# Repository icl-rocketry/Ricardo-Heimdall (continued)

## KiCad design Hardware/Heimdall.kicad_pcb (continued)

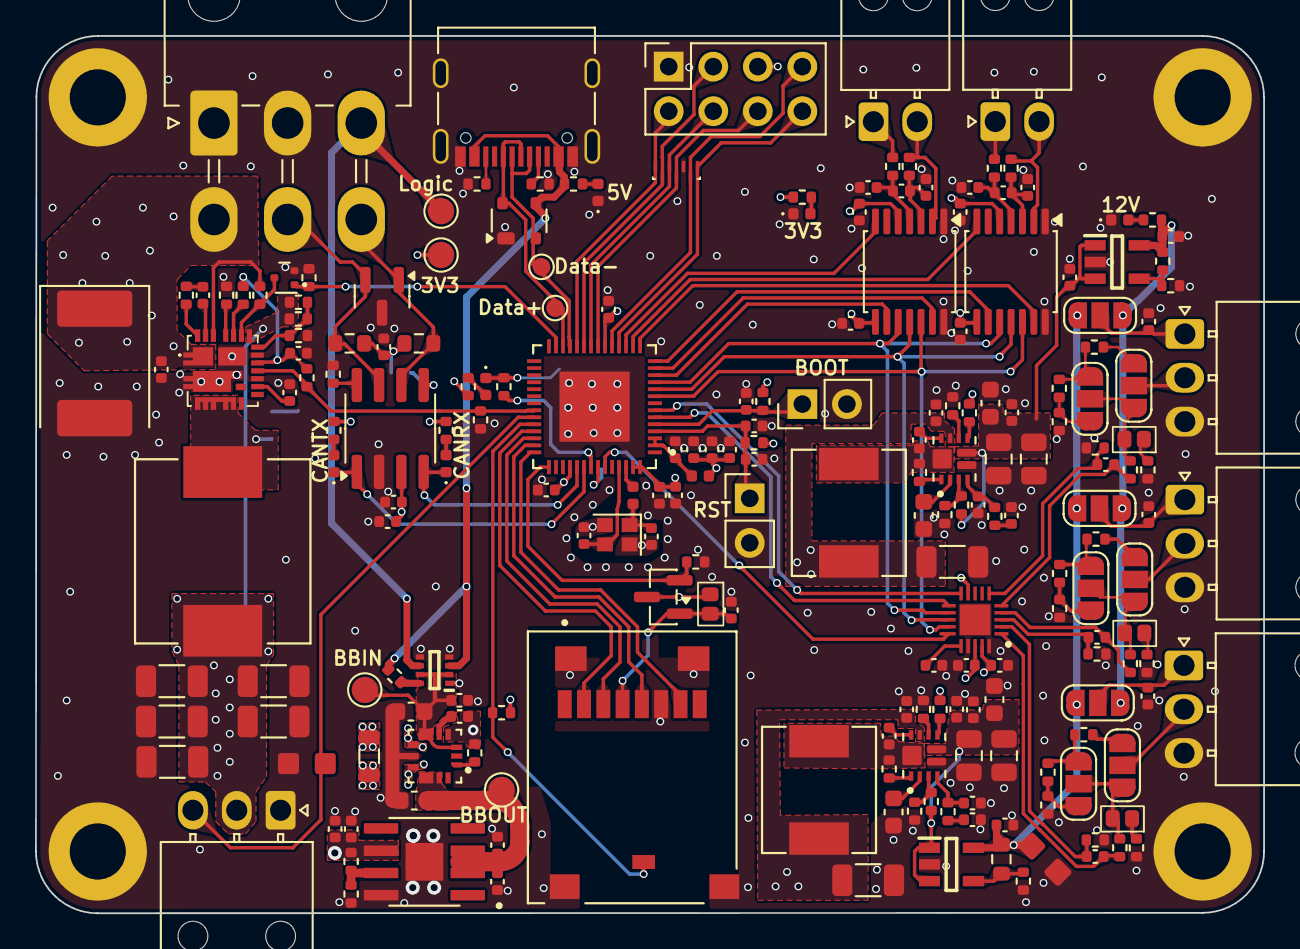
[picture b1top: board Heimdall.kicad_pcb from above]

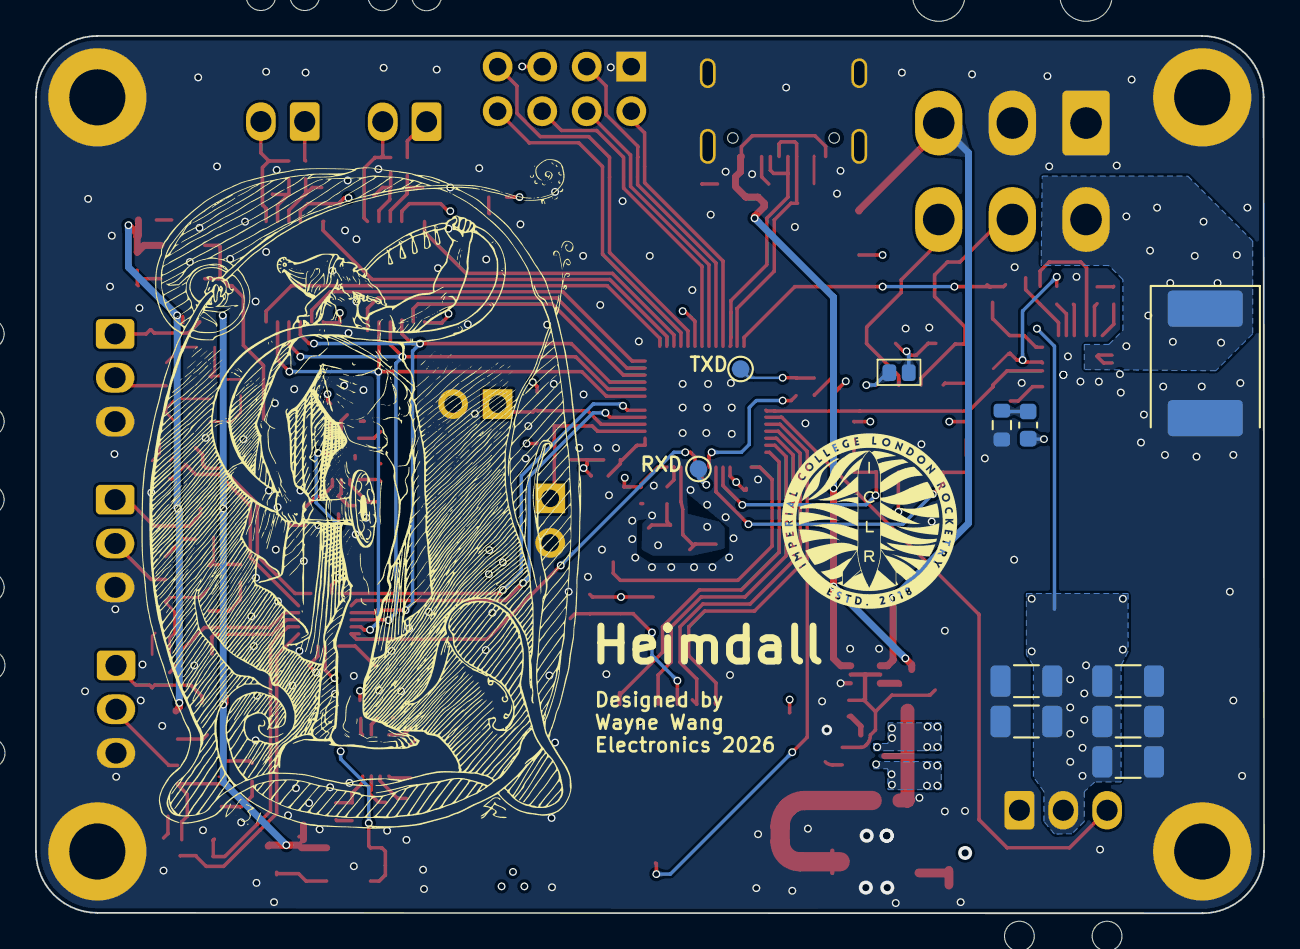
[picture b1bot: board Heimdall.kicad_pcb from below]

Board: 4 copper layers, 70.0 x 50.0 mm, 226 parts (12 on the bottom side), 139 nets.

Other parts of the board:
LOGO1: ICLR LOGO; iclr_logo_estd2018_10mm

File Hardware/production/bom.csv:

Designator,Footprint,Quantity,Value,LCSC Part #
"C101, C201, C205, C207, C502",0402,5,10uF,
"C102, C104, C107, C203, C301, C801, C802",0402,7,1uF,
"C103, C105, C106, C108, C110, C111, C208, C306, C310, C407, C409, C420, C421, C501, C701, C806, C807, C809, C902, C904, C905, C907, C909, C910",0402,24,100nF,
"C109, C804, C805, C808, C901, C903, C906, C908",0402,8,10nF,
"C112, C113",0402,2,11pF,
"C202, C414",0603,2,10uF,
C204,0603,1,22uF,
"C206, C302",0402,2,4.7uF,
"C303, C313",CP_EIA-7360-38_Kemet-E,2,100uF,T52M1107M035C0100
"C304, C305, C307, C308, C309, C312, C314, C315, C316, C317, C410",1206,11,47uF,
C311,0603,1,160pF,
C401,0603,1,2.2uF,
C402,0402,1,180pF,
C403,0402,1,3.9nF,
"C404, C413",0402,2,1uF,CL05X105KA5NQNC
"C405, C406, C417, C419",0805,4,22uF,
C408,0402,1,2.2uF, GRM155R61E225ME15D
C411,0603,1,10uF,TMK107BBJ106MA-T
"C412, C423",0402,2,100nF,C1005X5R1E104KT000E
C415,0402,1,120pF,
C416,0402,1,2.2nF,
C418,0402,1,2.2uF,GRM155R61E225ME15D
C422,0603,1,10uF, TMK107BBJ106MA-T
C424,1206,1,22uF,
C503,0402,1,47nF,
C803,0402,1,220nF,
D1001,RCLAMP3346PQTNT,1,RCLAMP3346PQTNT,
"D101, D102",0402,2,LED_GREEN,
D103,0402,1,LED_ORANGE,
D104,0402,1,LED_BLUE,
D105,0402,1,LED_RED,
D1101,CPD,1,CPDF3V3UP-HF,
D401,CPD,1,CPDF5V0U-HF,
D501,SOT-23,1,SM712_SOT23,
D601,SOT-143,1,SP0503BAHT,
D602,0402,1,LED_WHITE,
J103,Molex_Mini-Fit_Jr_5569-06A2_2x03_P4.20mm_Horizontal,1,RBUS,
"J1101, J801, J802, J803",Molex_Nano-Fit_105313-xx03_1x03_P2.50mm_Horizontal,4,1053131103,
J601,USB_C_Receptacle_Palconn_UTC16-G,1,USB_C_Receptacle_USB2.0,
J701,JAE_ST1W008S4TR2000,1,ST1W008S4TR2000,
"J901, J902",Molex_Nano-Fit_105313-xx02_1x02_P2.50mm_Horizontal,2,1053131102,
L101,0402,1,2nH,
L102,0402,1,20nH,
L201,0805,1,1uH,
L301,IND_SPM10065VT-3R3M-D,1,3.3uH,SPM10065VT-3R3M-D
"L401, L402",IND_SRP6540-390M,2,5uH,
LOGO1,iclr_logo_estd2018_10mm,1,ICLR LOGO,
Q301,SOT-723,1,"SSM3K15AMFV,L3F",
Q701,SOT-23,1,DMP3099L, DMP3099L
"R101, R105, R201, R204, R301, R303, R309, R404, R414, R702",0402,10,10kΩ,
"R102, R106",0402,2,470Ω,
"R103, R104, R305, R701, R807, R808, R811, R812, R816, R818",0402,10,1kΩ,
R107,0402,1,499Ω,
R108,0402,1,3kΩ,
R109,0402,1,18kΩ,
R202,0402,1,14kΩ,
R203,0402,1,56kΩ,
R302,0402,1,113kΩ,ERJ-2RKF1133X
R304,0402,1,2.2Ω,
R306,0402,1,442kΩ, ERJ-2RKF4423X 
R307,0402,1,200kΩ,
"R308, R403, R411",0402,3,100kΩ,
R310,0603,1,5.1Ω,
R401,0402,1,7.87kΩ,
R402,0402,1,360kΩ,
R405,0402,1,560kΩ,
"R406, R412",0402,2,49.9kΩ,
R407,0603,1,150kΩ,
R408,0402,1,301kΩ,
R409,0402,1,18.7kΩ,
R410,0402,1,976kΩ,
R413,0402,1,432kΩ,
R415,0402,1,475kΩ,
R416,0402,1,287kΩ,
R501,0402,1,0Ω,
"R502, R503",0603,2,60Ω,
"R601, R602, R603",0402,3,5.1kΩ,
"R801, R804, R813",0402,3,75kΩ,RT0402BRD0775KL
"R802, R805, R814",0402,3,14kΩ,0402WGF1402TCE
"R803, R806, R815",0402,3,10kΩ, ERA2ARB103X
"R809, R810, R817",0402,3,49.9Ω,RT0402BRD0749R9L
"R901, R902, R903, R904",0402,4,100Ω,
U101,QFN40P700X700X90-57N,1,ESP32-S3,
U201,SOTFL50P160X60-8N,1,LM66200DRLR,
U202,CONV_MAX77827AEFD+T,1,MAX77827AEFD+T,
U203,SOIC127P599X175-9N,1,SC4215ASTRT,
U301,SiC437BEDT1GE3,1,SiC437AED-T1,
U401,IC_TPS61089RNRR,1,TPS61089RNRR,
U402,SOT95P282X145-5N,1,AP2205-W5-7,
U403,SOT95P282X145-5N,1,AP2205-W5-7,AP2205-W5-7
U404,IC_TPS61089RNRR,1,TPS61089RNRR,TPS61089RNRR
U501,SOIC-8_3.9x4.9mm_P1.27mm,1,SN65HVD230,
U801,QFN40P300X300X80-21N-D,1,ADS131M04IRUKR,ADS131M04IRUKR
"U901, U902",TSSOP-14_4.4x5mm_P0.65mm,2,MAX31856,
Y101,Crystal_SMD_2016-4Pin_2.0x1.6mm,1,R940000171,

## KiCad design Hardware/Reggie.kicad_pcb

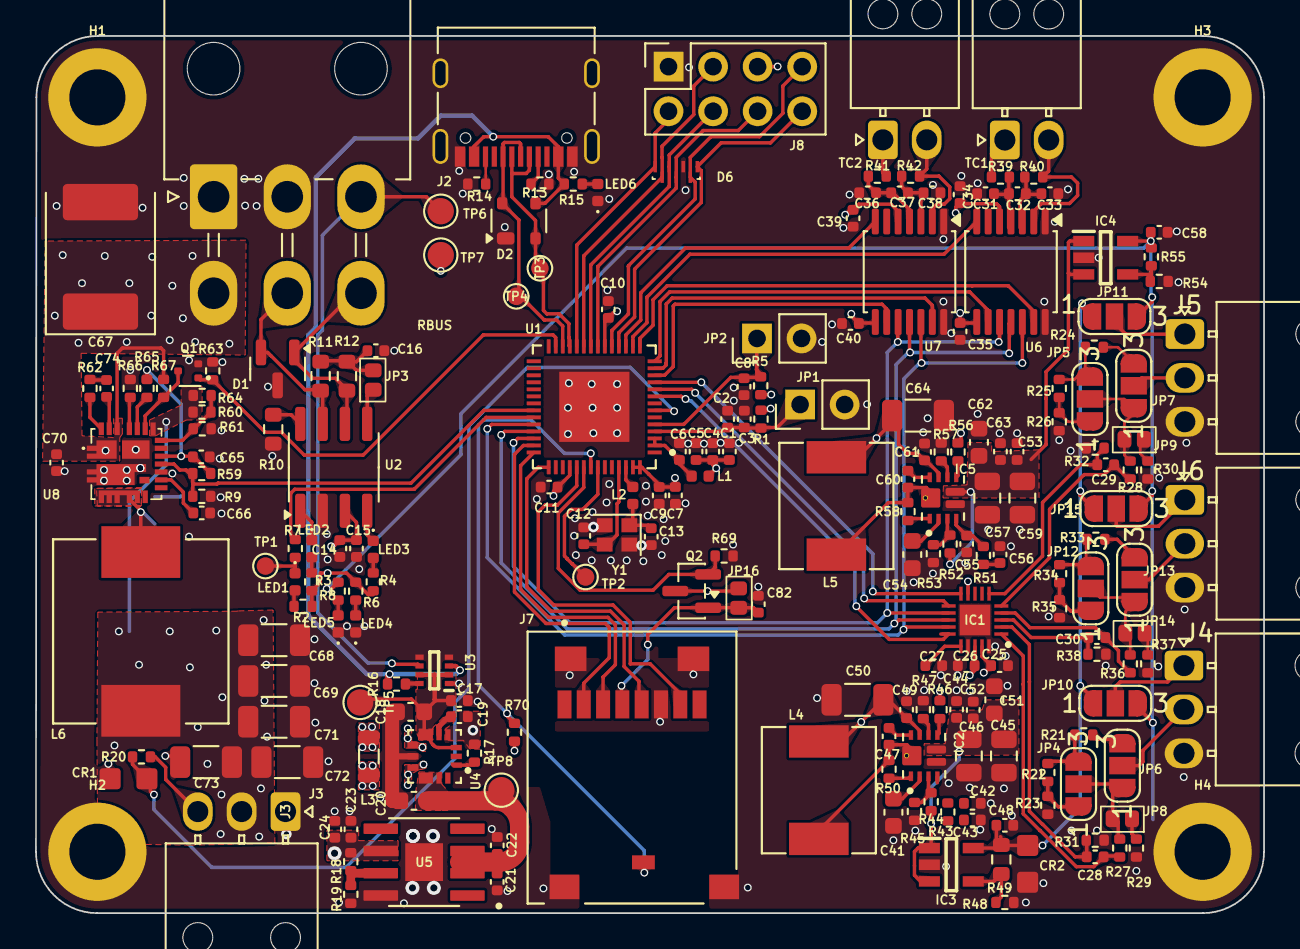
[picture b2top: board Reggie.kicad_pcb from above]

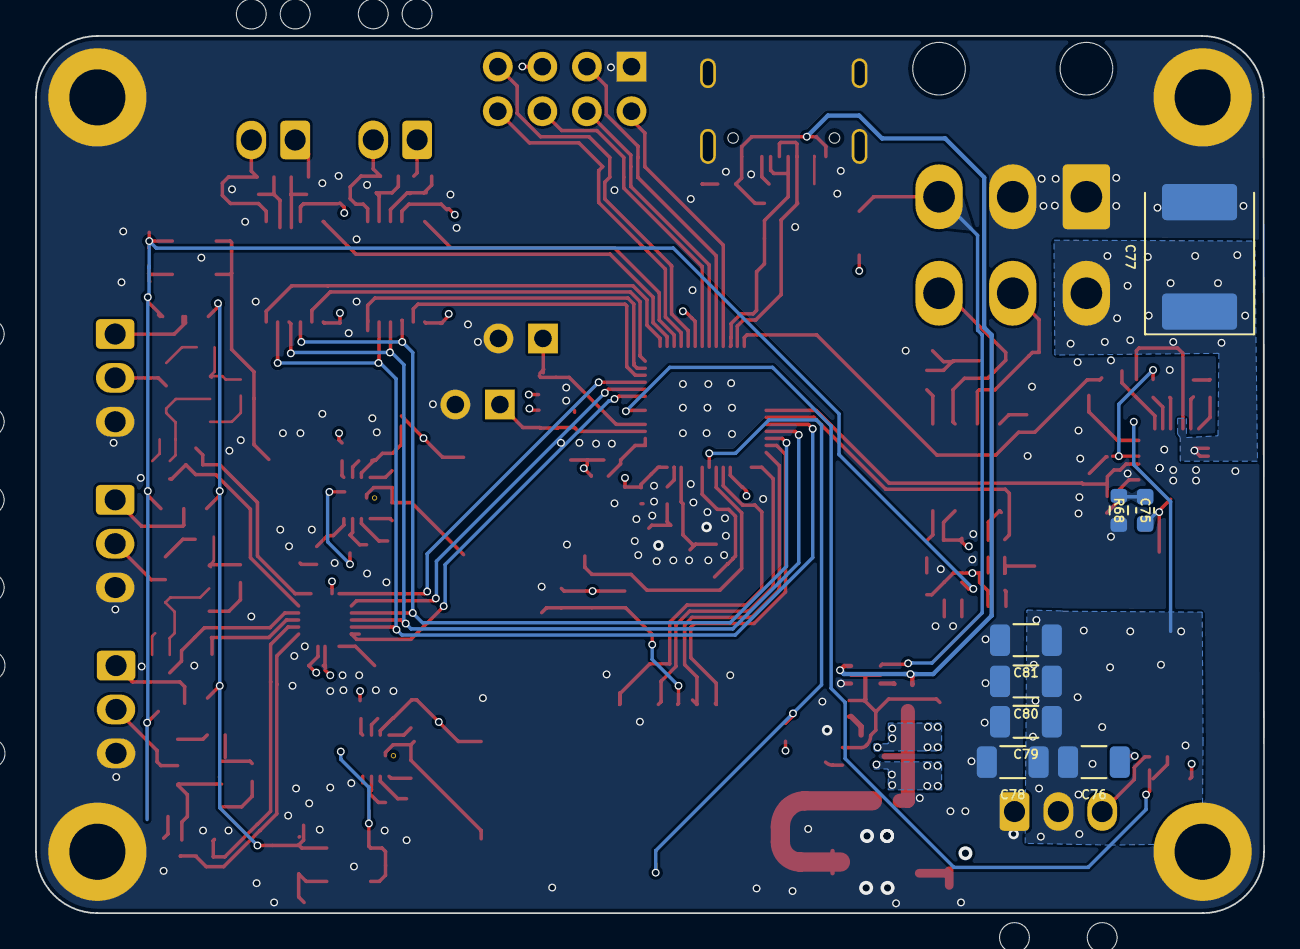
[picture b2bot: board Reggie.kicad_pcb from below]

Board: 4 copper layers, 70.0 x 50.0 mm, 223 parts (8 on the bottom side), 140 nets.

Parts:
C1, C15, C17, C21, C23: 10uF; C_0402_1005Metric
C2, C4, C7, C19, C25, C26, C44, C53, C65: 1uF; C_0402_1005Metric
C3, C5, C6, C8, C10, C11, C24, C32, C34, C35, C37, C39, C40, C74, C82: 0.1uF; C_0402_1005Metric
C9, C28, C29, C30: 10nF; C_0402_1005Metric
C12, C13: 11pF; C_0402_1005Metric
C14, C47, C49, C52, C60, C61, C63, C70: 100nF; C_0402_1005Metric
C16: 47nF; C_0402_1005Metric
C18, C51, C54, C62: 10uF; C_0603_1608Metric
C20: 22uF; C_0603_1608Metric
C22, C66: 4.7uF; C_0402_1005Metric
C27: 220nF; C_0402_1005Metric
C31, C33, C36, C38: 0.01uF; C_0402_1005Metric
C41: 2.2uF; C_0603_1608Metric
C42: 180pF; C_0402_1005Metric
C43: 3.9nF; C_0402_1005Metric
C45, C46, C57, C59: 22uF; C_0805_2012Metric
C48, C58: 2.2uF; C_0402_1005Metric
C50, C68, C69, C71, C72, C73, C76, C78, C79, C80, C81: 47uF; C_1206_3216Metric
C55: 120pF; C_0402_1005Metric
C56: 2.2nF; C_0402_1005Metric
C64: 22uF; C_1206_3216Metric
C67, C77: 100uF; CP_EIA-7360-38_Kemet-E
C75: 160pF; C_0603_1608Metric
CR1: CPDF3V3UP-HF; CPD
CR2: CPDF5V0U-HF; CPD
D1: SM712_SOT23; SOT-23
D2: SP0503BAHT; SOT-143
D6: RCLAMP3346PQTNT
H1, H2, H3, H4: MountingHole_Pad; MountingHole_3.2mm_M3_DIN965_Pad
IC1: ADS131M04IRUKR; QFN40P300X300X80-21N-D
IC2, IC5: TPS61089RNRR; IC_TPS61089RNRR
IC3, IC4: AP2205-W5-7; SOT95P282X145-5N
J1: RBUS; Molex_Mini-Fit_Jr_5569-06A2_2x03_P4.20mm_Horizontal
J2: USB_C_Receptacle_USB2.0; USB_C_Receptacle_Palconn_UTC16-G
J3: ServoConnector1; Molex_Nano-Fit_105313-xx03_1x03_P2.50mm_Horizontal
J4, J5, J6: 1053131104; Molex_Nano-Fit_105313-xx03_1x03_P2.50mm_Horizontal
J7: ST1W008S4TR2000; JAE_ST1W008S4TR2000
J8: GPIO Breakout; PinSocket_2x04_P2.54mm_Vertical
JP1, JP2: Conn_01x02_Male; PinHeader_1x02_P2.54mm_Vertical
JP3: TermJP; SmallerSolderJP
JP4, JP5, JP6, JP7, JP10, JP11, JP12, JP13, JP15: SolderJumper_3_Open; SolderJumper-3_P1.3mm_Open_RoundedPad1.0x1.5mm_NumberLabels
JP8, JP9, JP14, JP16: SolderJumper_2_Open; SmallerSolderJP
L1: 2.0nH; L_0402_1005Metric
L2: 20nH; L_0402_1005Metric
L3: 1uH; L_0805_2012Metric
L4, L5: SRR6038-5R0Y; IND_SRP6540-390M
L6: 3.3uH; IND_SPM10065VT-3R3M-D
LED1, LED2: GREEN_LED; LED_0402_1005Metric
LED3: ORANGE_LED; LED_0402_1005Metric
LED4: BLUE_LED; LED_0402_1005Metric
LED5: RED_LED; LED_0402_1005Metric
LED6: WHITE_LED; LED_0402_1005Metric
Q1: SSM3K15AMFV,L3F; SOT-723
Q2: PMOS; SOT-23
R1, R5, R46, R56: 10K; R_0402_1005Metric
R2, R6: 470; R_0402_1005Metric
R3, R4, R27, R28, R31, R32, R36, R38, R63, R69: 1k; R_0402_1005Metric
R7: 499R; R_0402_1005Metric
R8: 3k; R_0402_1005Metric
R9: 18k; R_0402_1005Metric
R10: 0; R_0603_1608Metric
R11, R12: 60; R_0603_1608Metric
R13, R14, R15: 5.1k; R_0402_1005Metric
R16, R19, R23, R26, R35, R59, R61, R67, R70: 10k; R_0402_1005Metric
R17, R22, R25, R34: 14k; R_0402_1005Metric
R18: 56k; R_0402_1005Metric
R20: 165; R_0402_1005Metric
R21, R24, R33: 75k; R_0402_1005Metric
R29, R30, R37: 49.9; R_0402_1005Metric
R39, R40, R41, R42: 100; R_0402_1005Metric
R43: 7.87k; R_0402_1005Metric
R44: 360k; R_0402_1005Metric
R45, R53, R66: 100k; R_0402_1005Metric
R47: 560k; R_0402_1005Metric
R48, R54: 49.9k; R_0402_1005Metric
R49: 150k; R_0603_1608Metric
R50: 301k; R_0402_1005Metric
R51: 18.7k; R_0402_1005Metric
R52: 976k; R_0402_1005Metric
R55: 432k; R_0402_1005Metric
R57: 475k; R_0402_1005Metric
R58: 287k; R_0402_1005Metric
R60: 113k; R_0402_1005Metric
R62: 2.2; R_0402_1005Metric
R64: 442k; R_0402_1005Metric
R65: 200k; R_0402_1005Metric
R68: 5.1R; R_0603_1608Metric
TC1, TC2: Thermocouple; Molex_Nano-Fit_105313-xx02_1x02_P2.50mm_Horizontal
TP1, TP2, TP3, TP4: TestPoint; TestPoint_Pad_D1.0mm
TP5, TP6, TP7, TP8: TestPoint; TestPoint_Pad_D1.5mm
U1: ESP32-S3; QFN40P700X700X90-57N
U2: SN65HVD230; SOIC-8_3.9x4.9mm_P1.27mm
U3: LM66200DRLR; SOTFL50P160X60-8N
U4: MAX77827AEFD+T; CONV_MAX77827AEFD+T
U5: SC4215ASTRT; SOIC127P599X175-9N
U6, U7: MAX31856; TSSOP-14_4.4x5mm_P0.65mm
U8: SiC437AED-T1; SiC437BEDT1GE3
Y1: R940000171; Crystal_SMD_2016-4Pin_2.0x1.6mm

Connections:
+3V3: C1.1, C4.1, C5.1, C7.1, C9.1, C10.1, C11.1, C14.1, C15.1, C23.2, C24.2, C25.2, C26.1, C34.2, C35.2, C39.2, C40.2, C49.1, C50.1, C61.1, C64.1, IC1.9 (~SYNC/~RESET), IC1.18 (DVDD), IC1.19 (AVDD), IC2.9 (VIN), IC5.9 (VIN), J8.5, JP16.1 (A), L1.1, L4.1, L5.1, Q2.3 (S), R1.1, R2.1, R3.1, R4.1, R5.1, R6.2, R18.1, R46.2, R56.2, R70.2, TP7.1, U1.20 (VDD3P3_RTC), U1.46 (VDD3P3_CPU), U1.55 (VDDA), U1.56 (VDDA), U2.3 (VCC), U5.6 (VOUT), U6.5 (AVDD), U6.8 (DVDD), U7.5 (AVDD), U7.8 (DVDD)
+5V: C48.1, CR2.2, IC3.5 (VOUT), JP10.1 (A), JP11.1 (A), JP15.1 (A), R49.2
+6V: C68.1, C69.1, C71.1, C72.1, C73.1, C76.2, C78.1, C79.1, C80.1, C81.1, J3.2, L6.1, R60.2, R64.2, U8.18 (V_OUT)
+12V: C58.1, IC4.5 (VOUT), JP10.3 (B), JP11.3 (B), JP15.3 (B), R8.1, R55.2
+16.8V: C67.1, C70.1, C77.1, J1.4, R67.2, U8.1 (V_IN_1), U8.2 (V_IN_2), U8.22 (VIN_1), U8.26 (VIN_2)
/ADS_CLK: IC1.15 (CLKIN), U1.9 (GPIO4/ADC1_CH3)
/ADS_CS: IC1.10 (~CS), U1.11 (GPIO6/ADC1_CH5)
/ADS_DRDY: IC1.11 (~DRDY), U1.10 (GPIO5/ADC1_CH4)
/BOOT: C8.1, JP2.1, R5.2, U1.5 (GPIO0/BOOT)
/BUCK_EN: Q1.1 (G), R63.2, U1.27 (GPIO21)
/Buck/BOOT: C74.1, U8.23 (BOOT)
/Buck/EN: Q1.3 (D), R67.1, U8.19 (EN)
/Buck/FB: R60.1, R61.2, R64.1, U8.17 (FB)
/Buck/PHASE: R62.1, U8.24 (PHASE)
/Buck/SW: C75.1, L6.2, U8.5 (SW_1), U8.6 (SW_2), U8.7 (SW_3), U8.8 (SW_4), U8.9 (SW_5), U8.30 (SW_6)
/Buck/VDD: C65.2, R59.1, R65.2, U8.15 (VDD)
/BuckPGOOD: R9.1, R59.2, U1.36 (SPICLK_N/GPIO48), U8.14 (P_GOOD)
/CAN+: D1.2 (A2), J1.5, R11.1, U2.7 (CANH)
/CAN-: D1.1 (A1), J1.6, R12.2, U2.6 (CANL)
/CAN-BUS/Vref: JP3.1 (A), U2.5 (Vref)
/CAN_RX: LED3.1 (K), U2.4 (R)
/CAN_TX: LED2.1 (K), U2.1 (D)
/CHIP_PU: C2.1, C3.1, JP1.1, R1.2, U1.4 (CHIP_PU/RESET)
/Data+: D2.4 (K), J2.A6 (D+), J2.B6 (D+), TP4.1, U1.26 (GPIO20/USB_D+/ADC2_CH9)
/Data-: D2.2 (K), J2.A7 (D-), J2.B7 (D-), TP3.1, U1.25 (GPIO19/USB_D-/ADC2_CH8)
/HSPI_MISO: IC1.13 (DOUT), U1.39 (GPIO34), U6.11 (SDO), U7.11 (SDO)
/HSPI_MOSI: IC1.14 (DIN), U1.38 (GPIO33), U6.12 (SDI), U7.12 (SDI)
/HSPI_SCLK: IC1.12 (SCLK), U1.40 (GPIO35), U6.10 (SCK), U7.10 (SCK)
/Power/BBIN: C17.1, C18.1, TP5.1, U3.2 (VOUT_1), U3.7 (VOUT_2), U4.3 (EN), U4.6 (IN)
/Power/BBOUT: C20.1, C21.1, C22.1, TP8.1, U4.11 (OUT), U4.13 (OUTS), U5.2 (EN), U5.3 (VIN)
/Power/BIAS: C19.1, U4.5 (BIAS)
/Power/FBIn: R18.2, R19.1, U5.7 (ADJ)
/Power/LX1: L3.1, U4.8 (LX1)
/Power/LX2: L3.2, U4.10 (LX2)
/Power/SEL: R17.1, U4.1 (SEL)
/Pressure/AIN0N: C28.2, IC1.2 (AIN0N), R31.2
/Pressure/AIN0P: C28.1, IC1.1 (AIN0P), R27.2
/Pressure/AIN1N: C30.2, IC1.3 (AIN1N), R38.2
/Pressure/AIN1P: C30.1, IC1.4 (AIN1P), R36.2
/Pressure/AIN2N: C29.2, IC1.6 (AIN2N), R32.2
/Pressure/AIN2P: C29.1, IC1.5 (AIN2P), R28.2
/RXD: TP2.1, U1.50 (U0RXD/PROG/GPIO44)
/SD_CS: J7.C2, U1.41 (GPIO36)
/SD_DET: J7.SW, R70.1, U1.49 (U0TXD/PROG/GPIO43)
/SD_EN: Q2.2 (G), R69.2, U1.48 (MTMS/JTAG/GPIO42)
/Sensor Power/FB_5V: IC2.3 (FB), R44.1, R45.2
/Sensor Power/FB_12V: IC5.3 (FB), R52.1, R53.2
/Sensor Power/LDO5.5V_IN: C44.1, C45.1, C46.1, C51.1, C52.1, IC2.6 (VOUT), IC3.1 (VIN), IC3.3 (EN), R44.2
/Sensor Power/LDO12V_IN: C53.1, C57.1, C59.1, C62.1, C63.1, IC4.1 (VIN), IC4.3 (EN), IC5.6 (VOUT), R52.2
/Sensor Power/SW_5V: IC2.1 (FSW), R50.1
/Sensor Power/SW_12V: IC5.1 (FSW), R58.1
/ServoPWM: CR1.2, R20.1, U1.7 (GPIO2/ADC1_CH1)
/TVS1: D6.1 (K/A_1), J8.8, U1.18 (GPIO13/ADC2_CH2)
/TVS3: D6.3 (K/A_2), J8.4, U1.22 (GPIO16/ADC2_CH5/XTAL_32K_N)
/TVS4: D6.4 (K/A_3), J8.2, U1.24 (GPIO18/ADC2_CH7/DAC_1)
/TVS5: D6.5 (K/A_4), J8.7, U1.19 (GPIO14/ADC2_CH3)
/TVS6: D6.6 (K/A_5), J8.6, U1.21 (GPIO15/ADC2_CH4/XTAL_32K_P)
/TVS7: D6.7 (K/A_6), J8.3, U1.23 (GPIO17/ADC2_CH6/DAC_2)
/TXD: LED1.1 (K), R7.1, TP1.1
/T_CS0: U1.12 (GPIO7/ADC1_CH6), U7.9 (~CS)
/T_CS1: U1.14 (GPIO9/ADC1_CH8), U6.9 (~CS)
/T_DRDY0: U1.17 (GPIO12/ADC2_CH1), U7.7 (~DRDY)
/T_DRDY1: U1.16 (GPIO11/ADC2_CH0), U6.7 (~DRDY)
/T_FAULT0: U1.13 (GPIO8/ADC1_CH7), U7.13 (~FAULT)
/T_FAULT1: U1.15 (GPIO10/ADC1_CH9), U6.13 (~FAULT)
/VSPI_MISO: J7.C7, U1.47 (MTDI/JTAG/GPIO41)
/VSPI_MOSI: J7.C3, U1.42 (GPIO37)
/VSPI_SCLK: J7.C5, U1.43 (GPIO38)
GND: C1.2, C2.2, C3.2, C4.2, C5.2, C6.2, C7.2, C8.2, C9.2, C10.2, C11.2, C12.2, C13.2, C14.2, C15.2, C16.2, C17.2, C18.2, C19.2, C20.2, C21.2, C22.2, C23.1, C24.1, C25.1, C26.2, C27.1, C31.1, C33.2, C34.1, C35.1, C36.1, C38.2, C39.1, C40.1, C41.2, C42.2, C43.2, C44.2, C45.2, C46.2, C48.2, C49.2, C50.2, C51.2, C52.2, C53.2, C54.2, C55.2, C56.2, C57.2, C58.2, C59.2, C61.2, C62.2, C63.2, C64.2, C65.1, C66.1, C67.2, C68.2, C69.2, C70.2, C71.2, C72.2, C73.2, C76.1, C77.2, C78.2, C79.2, C80.2, C81.2, C82.2, CR1.1, CR2.1, D1.3 (common), D2.1 (A), D6.2 (GND), H1.1, H2.1, H3.1, H4.1, IC1.17 (DGND), IC1.20 (AGND), IC1.21 (EP), IC2.5 (GND), IC3.2 (GND), IC4.2 (GND), IC5.5 (GND), J1.1, J1.2, J2.A1 (GND), J2.A12 (GND), J2.B1 (GND), J2.B12 (GND), J2.S1 (SHIELD), J3.1, J4.3, J5.3, J6.3, J7.C6, J7.GND1 (GND), J7.GND2 (GND), J7.GND3 (GND), J7.GND4 (GND), J8.1, JP1.2, JP2.2, LED4.1 (K), LED5.1 (K), LED6.1 (K), Q1.2 (S), R9.2, R10.2, R13.2, R14.1, R17.2, R19.2, R23.1, R26.1, R29.2, R30.2, R31.1, R32.1, R35.1, R37.2, R38.1, R45.1, R47.1, R48.1, R53.1, R54.1, R57.1, R61.1, R63.1, R66.2, R68.2, R69.1, U1.57 (GND), U2.2 (GND), U3.1 (GND_1), U3.4 (~ON), U3.5 (GND_2), U4.4 (AGND), U4.9 (PGND), U5.8 (GND), U5.9 (GND), U6.1 (AGND), U6.14 (DGND), U7.1 (AGND), U7.14 (DGND), U8.3 (P_GND_1), U8.4 (P_GND_2), U8.13 (P_GND_3), U8.16 (A_GND), U8.25 (AGND), U8.27 (PGND), U8.29 (P_GND_4), Y1.2, Y1.4
unnamed: C6.1, L1.2, U1.2 (VDD3P3), U1.3 (VDD3P3)
unnamed: C13.1, L2.2, Y1.1
unnamed: C43.1, R43.2
unnamed: C56.1, R51.2
unnamed: C74.2, R62.2
unnamed: C75.2, R68.1
unnamed: C27.2, IC1.16 (CAP)
unnamed: C47.1, IC2.10 (BOOT)
unnamed: C42.1, IC2.4 (COMP), R43.1
unnamed: IC2.7 (EN), R46.1
unnamed: IC2.8 (ILIM), R47.2
unnamed: C47.2, IC2.11 (SW), L4.2, R50.2
unnamed: C41.1, IC2.2 (VCC)
unnamed: IC3.4 (ADJ/NC), R48.2, R49.1
unnamed: IC4.4 (ADJ/NC), R54.2, R55.1
unnamed: C60.1, IC5.10 (BOOT)
unnamed: C55.1, IC5.4 (COMP), R51.1
unnamed: IC5.7 (EN), R56.1
unnamed: IC5.8 (ILIM), R57.2
unnamed: C60.2, IC5.11 (SW), L5.2, R58.2
unnamed: C54.1, IC5.2 (VCC)
unnamed: J2.A5 (CC1), R13.1
unnamed: J2.B5 (CC2), R14.2
unnamed: J3.3, R20.2
unnamed: J4.1, JP10.2 (C)
unnamed: J4.2, JP6.2 (C)
unnamed: J5.1, JP11.2 (C)
unnamed: J5.2, JP7.2 (C)
unnamed: J6.1, JP15.2 (C)
unnamed: J6.2, JP13.2 (C)
unnamed: C16.1, JP3.2 (B), R11.2, R12.1
unnamed: JP4.1 (A), R22.2, R23.2
unnamed: JP4.3 (B), R21.2, R22.1
unnamed: JP4.2 (C), JP6.1 (A), JP8.2 (B), R27.1
unnamed: JP5.1 (A), R25.2, R26.2
unnamed: JP5.3 (B), R24.2, R25.1
unnamed: JP5.2 (C), JP7.1 (A), JP9.2 (B), R28.1
unnamed: JP6.3 (B), R21.1
unnamed: JP7.3 (B), R24.1
unnamed: JP8.1 (A), R29.1
unnamed: JP9.1 (A), R30.1
unnamed: JP12.1 (A), R34.2, R35.2
unnamed: JP12.3 (B), R33.2, R34.1
unnamed: JP12.2 (C), JP13.1 (A), JP14.2 (B), R36.1
unnamed: JP13.3 (B), R33.1
unnamed: JP14.1 (A), R37.1
unnamed: C82.1, J7.C4, JP16.2 (B), Q2.1 (D)
unnamed: LED1.2 (A), R2.2
unnamed: LED2.2 (A), R3.2
unnamed: LED3.2 (A), R4.2
unnamed: LED4.2 (A), R6.1
unnamed: LED5.2 (A), R8.2
unnamed: LED6.2 (A), R15.2
unnamed: R39.2, TC1.1 (+)
unnamed: R40.1, TC1.2 (-), U6.2 (BIAS)
unnamed: R41.2, TC2.1 (+)
unnamed: R42.1, TC2.2 (-), U7.2 (BIAS)
unnamed: R7.2, U1.37 (SPICLK_P/GPIO47)
unnamed: C12.1, U1.53 (XTAL_N), Y1.3
unnamed: L2.1, U1.54 (XTAL_P)
unnamed: R10.1, U2.8 (Rs)
unnamed: R16.2, U3.8 (ST)
unnamed: C31.2, C32.1, R39.1, U6.4 (T+)
unnamed: C32.2, C33.1, R40.2, U6.3 (T-)
unnamed: C36.2, C37.1, R41.1, U7.4 (T+)
unnamed: C37.2, C38.1, R42.2, U7.3 (T-)
unnamed: R65.1, U8.20 (MODE_2)
unnamed: C66.2, U8.12 (V_DRV)
unnamed: R66.1, U8.21 (_MODE_1)
RBUS_uC_V: J1.3, TP6.1, U3.6 (VIN2)
VBUS: D2.3 (K), J2.A4 (VBUS), J2.A9 (VBUS), J2.B4 (VBUS), J2.B9 (VBUS), R15.1, R16.1, U3.3 (VIN1)

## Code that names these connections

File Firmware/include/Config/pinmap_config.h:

/*
**********************
* PINS               *
**********************
 */
#pragma once
#include <stdint.h>

namespace PinMap{
    
    static constexpr uint8_t ADC_DRDY = 1;
    static constexpr uint8_t ADC_CS   = 2;
    static constexpr uint8_t HSPI_MOSI = 4;
    static constexpr uint8_t HSPI_MISO = 5;
    static constexpr uint8_t HSPI_SCLK = 6;
    static constexpr uint8_t T_CS_0 = 7;
    static constexpr uint8_t T_FAULT_0 = 8;
    static constexpr uint8_t T_CS_1 = 9;
    static constexpr uint8_t T_FAULT_1 = 10;
    static constexpr uint8_t T_DRDY_1 = 11;
    static constexpr uint8_t T_DRDY_0 = 12;
    static constexpr uint8_t GPIO_1 = 13;
    static constexpr uint8_t GPIO_5 = 14;
    static constexpr uint8_t GPIO_6 = 15;
    static constexpr uint8_t GPIO_3 = 16;
    static constexpr uint8_t GPIO_7 = 17;
    static constexpr uint8_t GPIO_4 = 18;
    static constexpr uint8_t BUCK_EN = 21;

    static constexpr uint8_t SD_DET = 33;
    static constexpr uint8_t SD_CS = 34;
    static constexpr uint8_t VSPI_MOSI = 35;
    static constexpr uint8_t VSPI_SCLK = 36;
    static constexpr uint8_t VSPI_MISO = 37;
    static constexpr uint8_t SD_EN = 38;

    static constexpr uint8_t ADC_CLK = 45;
    static constexpr uint8_t SERVO_PWM = 47;
    static constexpr uint8_t BUCK_PGOOD = 48;




    static constexpr uint8_t TX_CAN = 42 ;
    static constexpr uint8_t RX_CAN = 41;

};

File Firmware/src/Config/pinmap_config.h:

/*
**********************
* PINS               *
**********************
 */
#pragma once

// Heimdall V1 Pinmap

namespace PinMap{

    static constexpr int SNSR_MISO = 5;
    static constexpr int SNSR_MOSI = 4;
    static constexpr int SNSR_SCLK = 6;

    static constexpr int TC0_Cs = 7;
    // static constexpr int TC1_Cs = 8;

    static constexpr int ADC0_Cs = 2;
    static constexpr int ADC_CLK = 45;

    static constexpr int SD_SCLK = 36;
    static constexpr int SD_MISO = 37;
    static constexpr int SD_MOSI = 35;
    static constexpr int SdDet_0 = 33;
    static constexpr int SdCs_0 = 34;
    static constexpr int SD_EN = 38;

    static constexpr int TxCan = 42;
    static constexpr int RxCan = 41;

    static constexpr int BuckEN = 21;
    static constexpr int BuckPGOOD = 48;
    static constexpr int ServoPWM = 47;

    static constexpr int BuckSense = 13;
};

// Stark V3 Pinmap

// namespace PinMap{

//     static constexpr int SNSR_MISO = 33 ;
//     static constexpr int SNSR_MOSI = 34;
//     static constexpr int SNSR_SCLK = 47;

//     static constexpr int TC0_Cs = 48;
//     // static constexpr int TC1_Cs = 8;

//     static constexpr int ADC0_Cs = 36;
//     static constexpr int ADC_CLK = 37;

//     static constexpr int SD_SCLK = 16;
//     static constexpr int SD_MISO = 15;
//     static constexpr int SD_MOSI = 17;
//     static constexpr int SdDet_0 = 39;
//     static constexpr int SdCs_0 = 34;
//     // static constexpr int SD_EN = 38;

//     static constexpr int TxCan = 11;
//     static constexpr int RxCan = 10;

//     // static constexpr int BuckEN = 21;
//     // static constexpr int BuckPGOOD = 48;
//     static constexpr int ServoPWM = 13;

//     // static constexpr int BuckSense = 13;
// };

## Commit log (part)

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2026-01-13 Updated connections
2026-01-20 new TVS
2026-02-10 2nd review of schematic
2026-02-24 pcb update
2026-03-03 pcb and schematic update
    Found all footprints including J3, pressure controller, tvs diode. PCB infrastructure update
2026-03-07 PCB update
    packing update
2026-03-07 schematic changes and updated tvs footprints
2026-03-12 Overall Packing Complete!!
    Version1
2026-05-03 Overall Packing Backup Version
2026-05-18 Overall Routing Complete!!!
    Version2
2026-06-01 Routing Improvement
    Version 3. Mainly solved 3 problem: 1. clock and decoupler closer to microcontroller; 2. Route of Data+ and Data- neater; 3. wider trace for 6v and 16.8v
2026-06-03 Filled zones and via location
    Version 4. allocate filled zones and vias, also reassigned pins from microcontroller
2026-06-04 via improvement and footprint allocation
    Version 4.1
2026-06-16 Version 4.2
    Rename from Reggie to Heimdall and other improvements
2026-06-16 Version 4.3
    Redundant file deleted
